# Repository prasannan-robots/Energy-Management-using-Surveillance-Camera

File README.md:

# Energy-Management-using-Surveillance-Camera
This is a project which uses camera to detect the humans and control indoor appliances

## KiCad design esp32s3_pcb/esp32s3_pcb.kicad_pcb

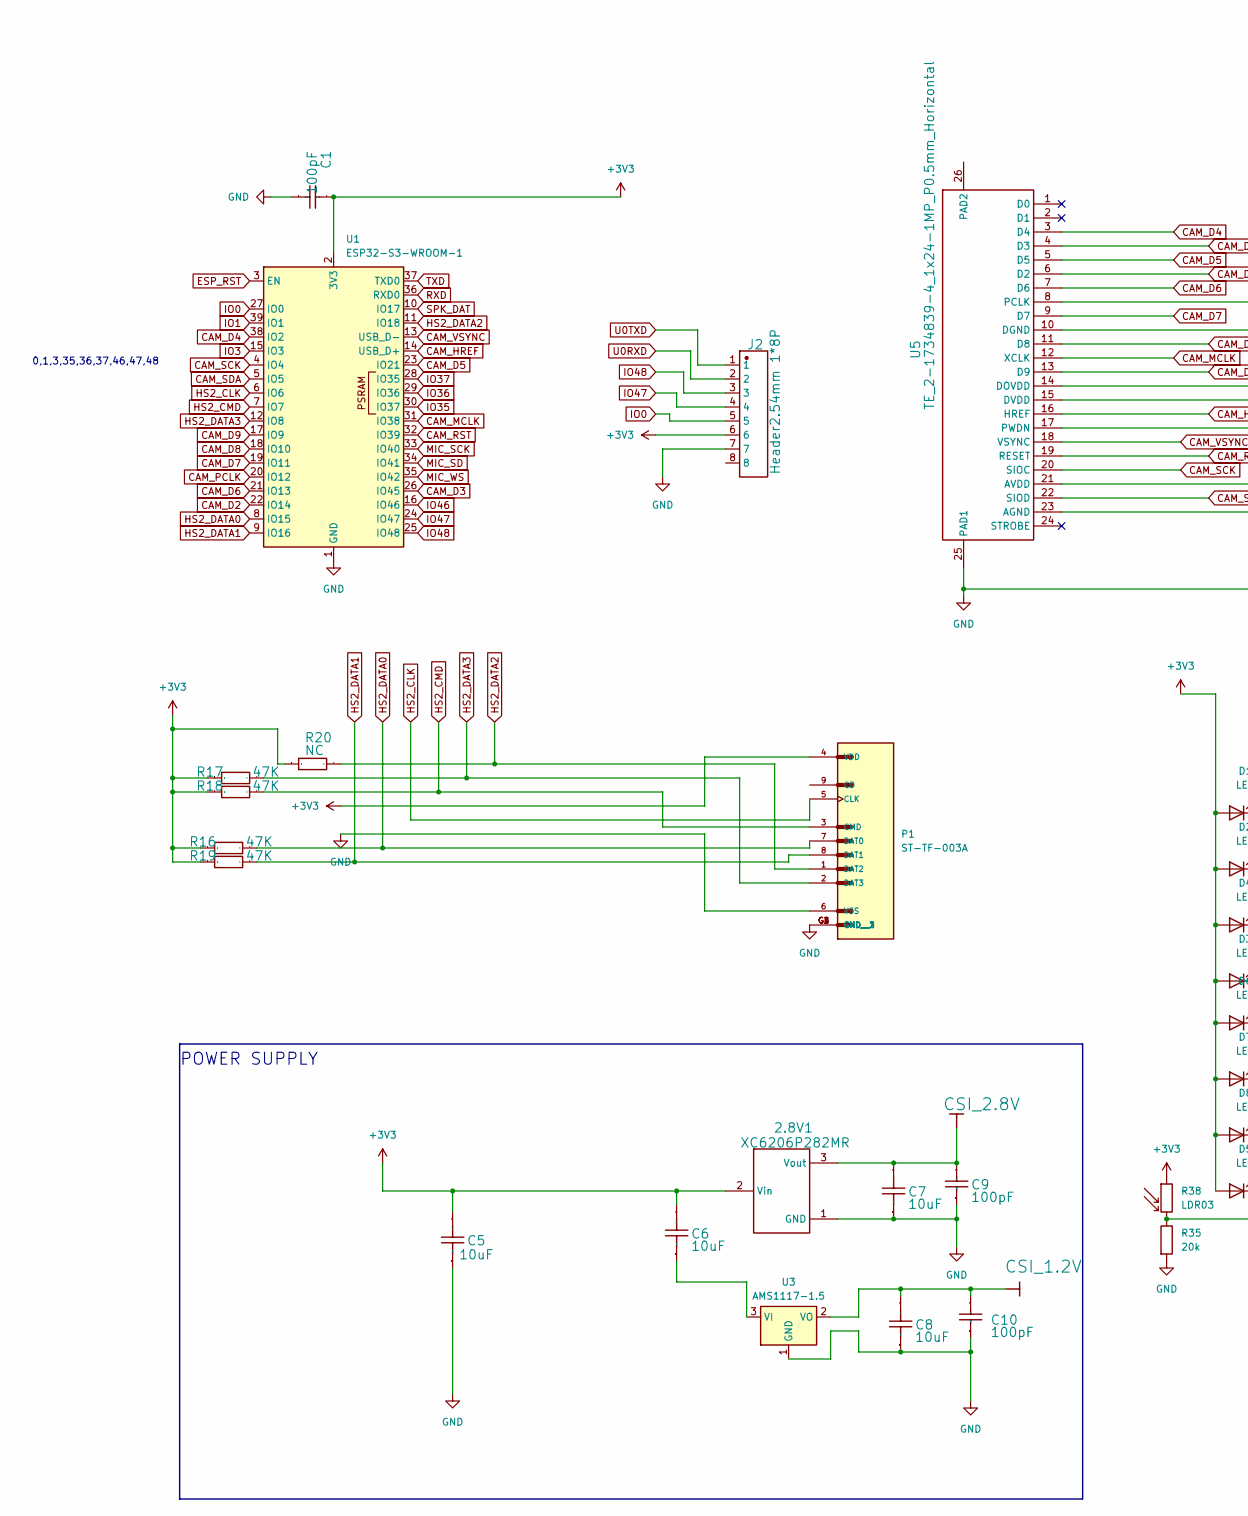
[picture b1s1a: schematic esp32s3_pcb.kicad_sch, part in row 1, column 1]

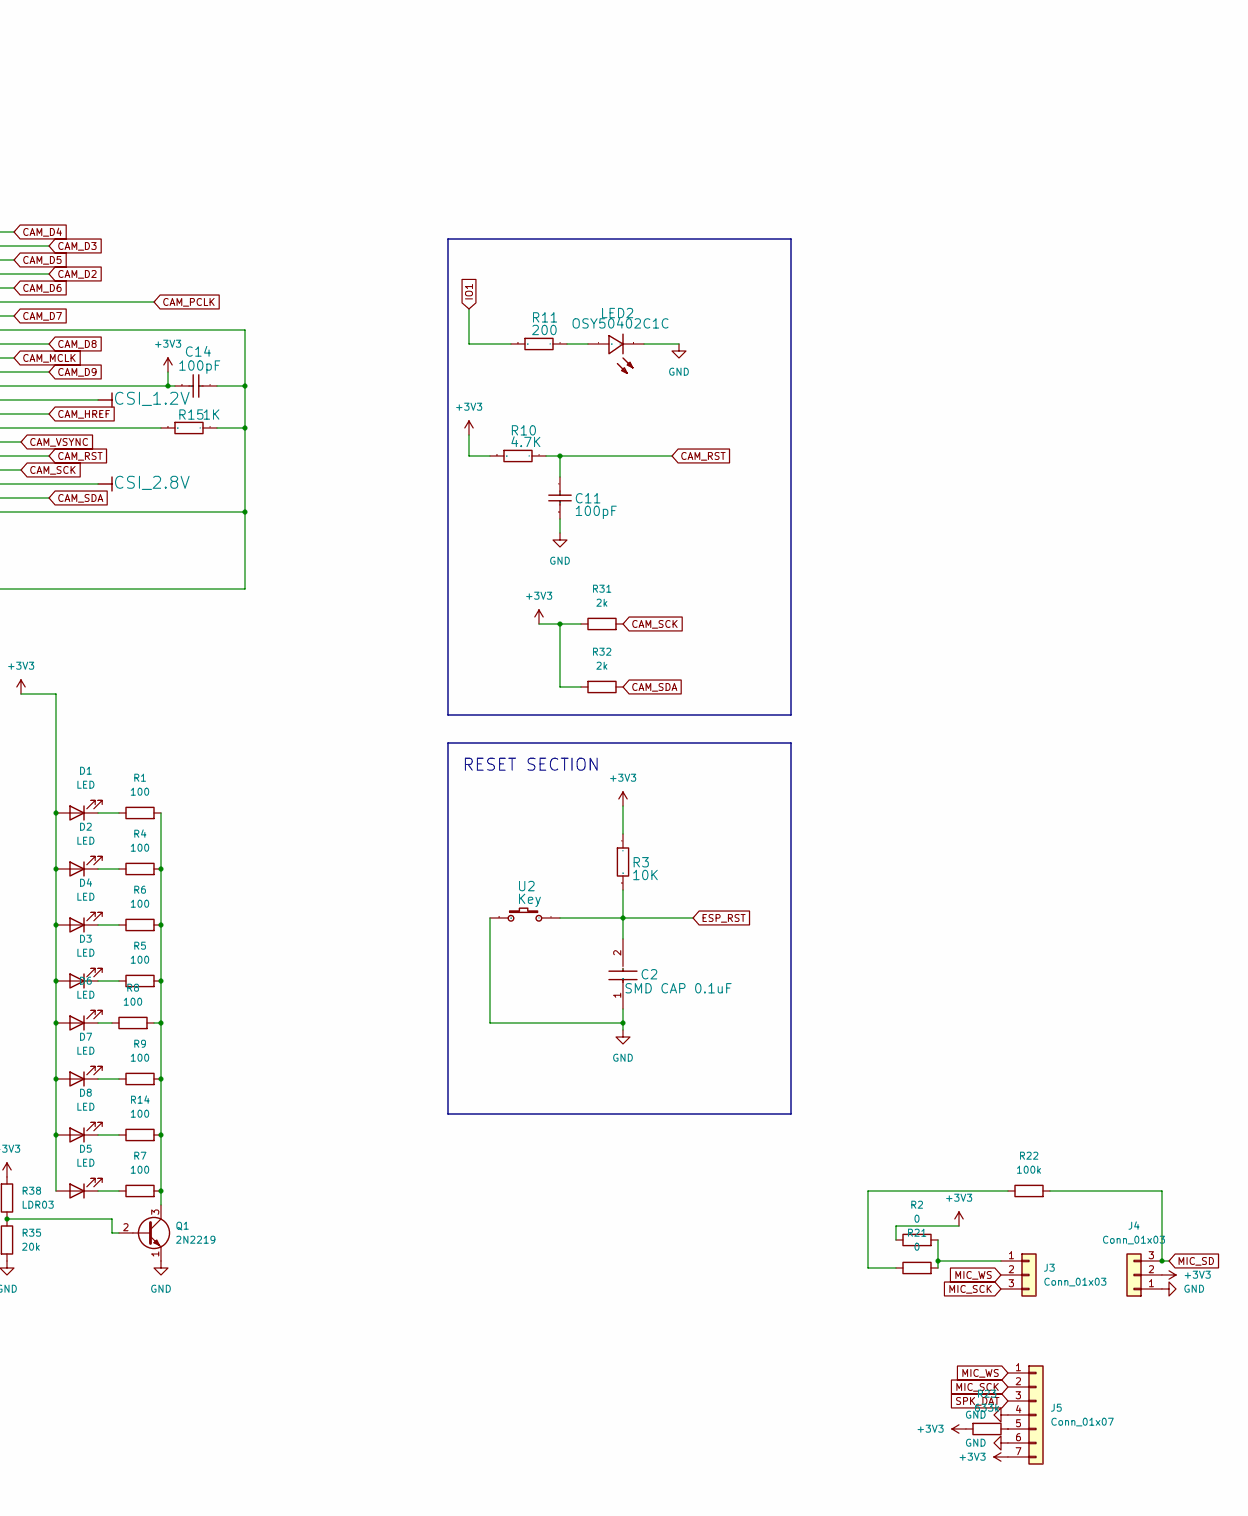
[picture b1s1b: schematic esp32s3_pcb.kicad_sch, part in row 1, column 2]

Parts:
2.8V1: XC6206P282MR; SOT-23-3; Manufacturer Part XC6206P282MR
C1, C9, C10, C11, C14: 100pF; C_0603_1608Metric; Manufacturer Part 0402CG101J500NT
C2: SMD CAP 0.1uF; C_0603_1608Metric
C5, C6, C7, C8: 10uF; C_0603_1608Metric; Manufacturer Part 0805F106M160NT
D1, D2, D3, D4, D5, D6, D7, D8: LED; LED_D5.0mm_IRGrey
J2: Header2.54mm 1*8P; PinSocket_1x08_P2.54mm_Vertical; Manufacturer Part Header2.54mm 1*8P
J3, J4: Conn_01x03; PinSocket_1x03_P2.54mm_Vertical
J5: Conn_01x07; PinSocket_1x07_P2.54mm_Vertical
LED2: OSY50402C1C; LED_D5.0mm; Manufacturer Part OSY50402C1C
P1: ST-TF-003A; SUNTECH_ST-TF-003A
Q1: 2N2219; TO-46-3_Window
R1, R4, R5, R6, R7, R8, R9, R14: 100; R_0402_1005Metric
R2, R21: 0; R_0402_1005Metric
R3: 10K; R_0805_2012Metric; Manufacturer Part RC0201JR-0710KL
R10: 4.7K; R_0402_1005Metric; Manufacturer Part 0402WGF4701TCE
R11: 200; R_0402_1005Metric; Manufacturer Part 0805W8F1001T5E
R15: 1K; R_0402_1005Metric; Manufacturer Part 0805W8F1001T5E
R16, R17, R18, R19: 47K; R_0402_1005Metric; Manufacturer Part MCR004YZPJ473
R20: NC; R_0402_1005Metric
R22: 100k; R_0402_1005Metric
R23: 633k; R_0603_1608Metric
R31, R32: 2k; R_0603_1608Metric
R35: 20k; R_0603_1608Metric
R38: LDR03; R_LDR_5.1x4.3mm_P3.4mm_Vertical
U1: ESP32-S3-WROOM-1
U2: Key; PinHeader_1x02_P2.54mm_Vertical
U3: AMS1117-1.5; SOT-89-3
U5: TE_2-1734839-4_1x24-1MP_P0.5mm_Horizontal

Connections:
+3V3: 2.8V1.2 (Vin), C1.2, C5.2, C6.2, C14.1, D1.2 (A), D2.2 (A), D3.2 (A), D4.2 (A), D5.2 (A), D6.2 (A), D7.2 (A), D8.2 (A), J2.6, J4.2, J5.7, P1.4 (VDD), R2.1, R3.2, R10.1, R16.1, R17.1, R18.1, R19.1, R20.1, R23.2, R31.1, R32.2, R38.1, U1.2 (3V3), U5.14 (DOVDD)
CAM_D2: U1.22 (IO14), U5.6 (D2)
CAM_D3: U1.26 (IO45), U5.4 (D3)
CAM_D4: U1.38 (IO2), U5.3 (D4)
CAM_D5: U1.23 (IO21), U5.5 (D5)
CAM_D6: U1.21 (IO13), U5.7 (D6)
CAM_D7: U1.19 (IO11), U5.9 (D7)
CAM_D8: U1.18 (IO10), U5.11 (D8)
CAM_D9: U1.17 (IO9), U5.13 (D9)
CAM_HREF: U1.14 (USB_D+), U5.16 (HREF)
CAM_MCLK: U1.31 (IO38), U5.12 (XCLK)
CAM_PCLK: U1.20 (IO12), U5.8 (PCLK)
CAM_RST: C11.2, R10.2, U1.32 (IO39), U5.19 (RESET)
CAM_SCK: R31.2, U1.4 (IO4), U5.20 (SIOC)
CAM_SDA: R32.1, U1.5 (IO5), U5.22 (SIOD)
CAM_VSYNC: U1.13 (USB_D-), U5.18 (VSYNC)
CSI_1.2V: C8.2, C10.2, U3.2 (VO), U5.15 (DVDD)
CSI_2.8V: 2.8V1.3 (Vout), C7.2, C9.2, U5.21 (AVDD)
ESP_RST: C2.2, R3.1, U1.3 (EN), U2.2
GND: 2.8V1.1 (GND), C1.1, C2.1, C5.1, C7.1, C8.1, C9.1, C10.1, C11.1, C14.2, J2.7, J4.1, J5.4, J5.6, LED2.1 (C), P1.6 (VSS), P1.G1 (GND), P1.G2 (GND__1), P1.G3 (GND__2), P1.G4 (GND__3), Q1.1 (E), R15.2, R35.2, U1.1 (GND), U1.40 (GND), U1.41 (GND), U2.1, U3.1 (GND), U5.10 (DGND), U5.23 (AGND), U5.25 (PAD1)
HS2_CLK: P1.5 (CLK), U1.6 (IO6)
HS2_CMD: P1.3 (CMD), R18.2, U1.7 (IO7)
HS2_DATA0: P1.7 (DAT0), R16.2, U1.8 (IO15)
HS2_DATA1: P1.8 (DAT1), R19.2, U1.9 (IO16)
HS2_DATA2: P1.1 (DAT2), R20.2, U1.11 (IO18)
HS2_DATA3: P1.2 (DAT3), R17.2, U1.12 (IO8)
IO0: J2.5, U1.27 (IO0)
IO1: R11.1, U1.39 (IO1)
IO3: U1.15 (IO3)
IO35: U1.30 (IO37)
IO36: U1.29 (IO36)
IO37: U1.28 (IO35)
IO46: U1.16 (IO46)
IO47: J2.4, U1.24 (IO47)
IO48: J2.3, U1.25 (IO48)
MIC_SCK: J3.3, J5.2, U1.33 (IO40)
MIC_SD: J4.3, R22.2, U1.34 (IO41)
MIC_WS: J3.2, J5.1, U1.35 (IO42)
unnamed: D1.1 (K), R1.1
unnamed: D2.1 (K), R4.1
unnamed: D3.1 (K), R5.1
unnamed: D4.1 (K), R6.1
unnamed: D5.1 (K), R7.1
unnamed: D6.1 (K), R8.1
unnamed: D7.1 (K), R9.1
unnamed: D8.1 (K), R14.1
unnamed: J3.1, R2.2, R21.2
unnamed: J5.5, R23.1
unnamed: LED2.2 (A), R11.2
unnamed: Q1.2 (B), R35.1, R38.2
unnamed: Q1.3 (C), R1.2, R4.2, R5.2, R6.2, R7.2, R8.2, R9.2, R14.2
unnamed: R21.1, R22.1
unnamed: C6.1, U3.3 (VI)
unnamed: R15.1, U5.17 (PWDN)
RXD: U1.36 (RXD0)
SPK_DAT: J5.3, U1.10 (IO17)
TXD: U1.37 (TXD0)
U0RXD: J2.2
U0TXD: J2.1

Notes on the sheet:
RESET SECTION
0,1,3,35,36,37,46,47,48
POWER SUPPLY

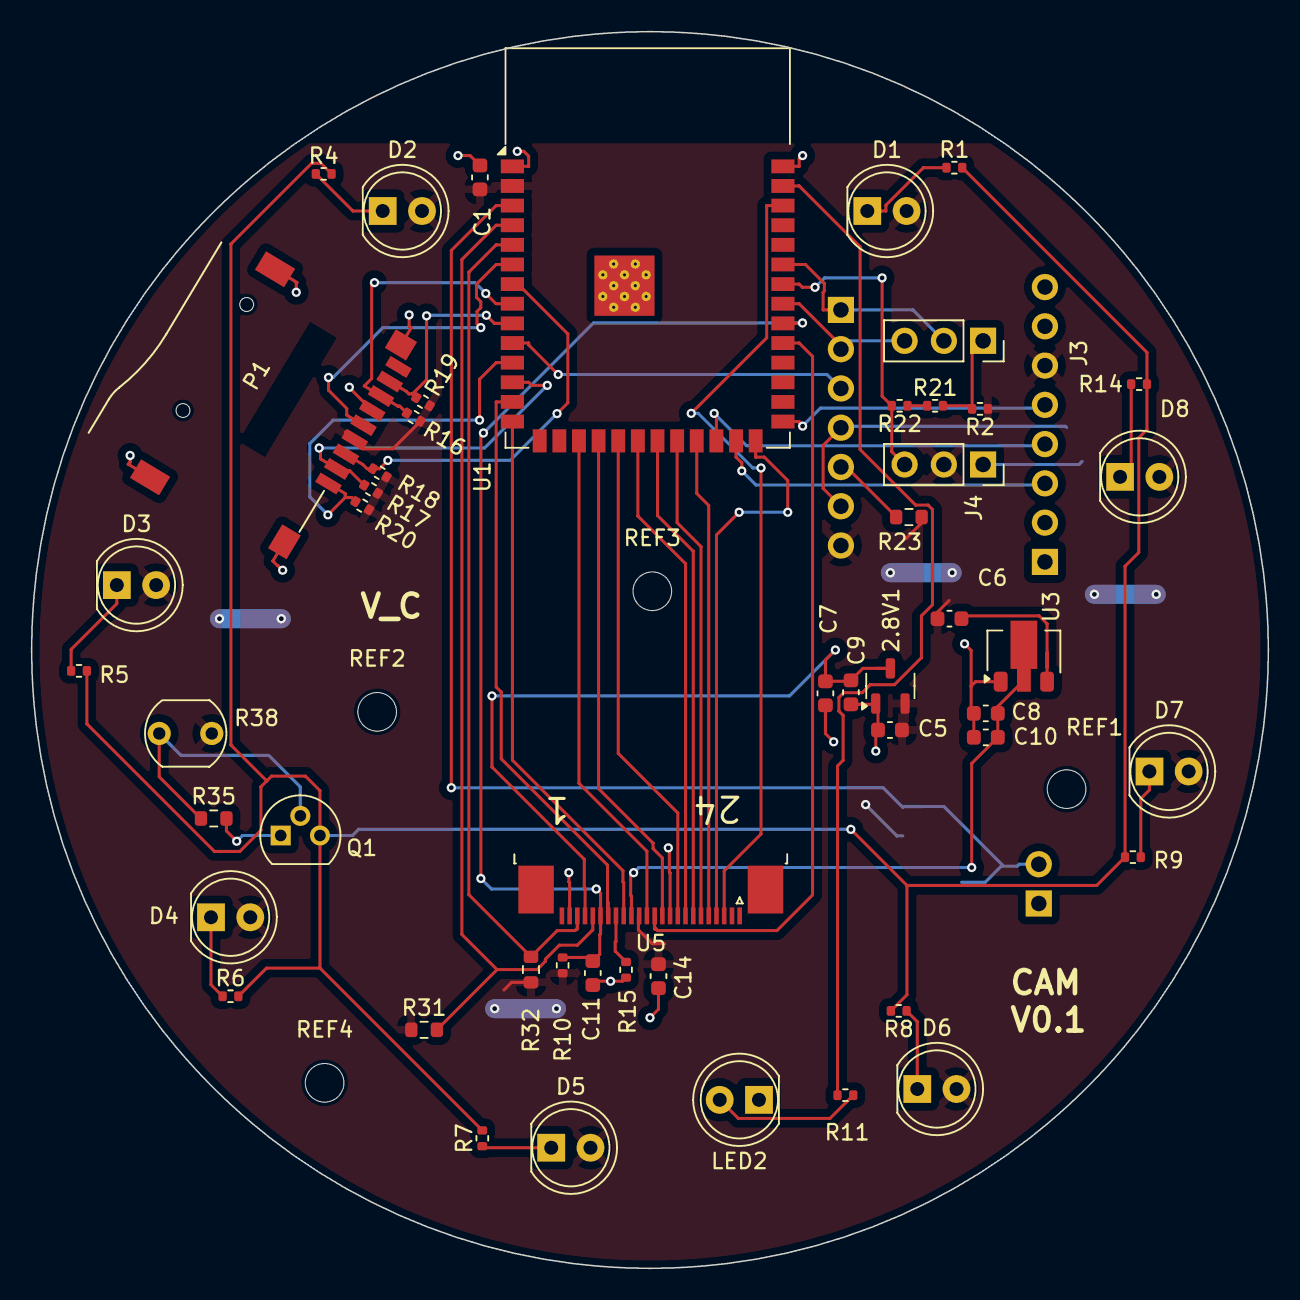
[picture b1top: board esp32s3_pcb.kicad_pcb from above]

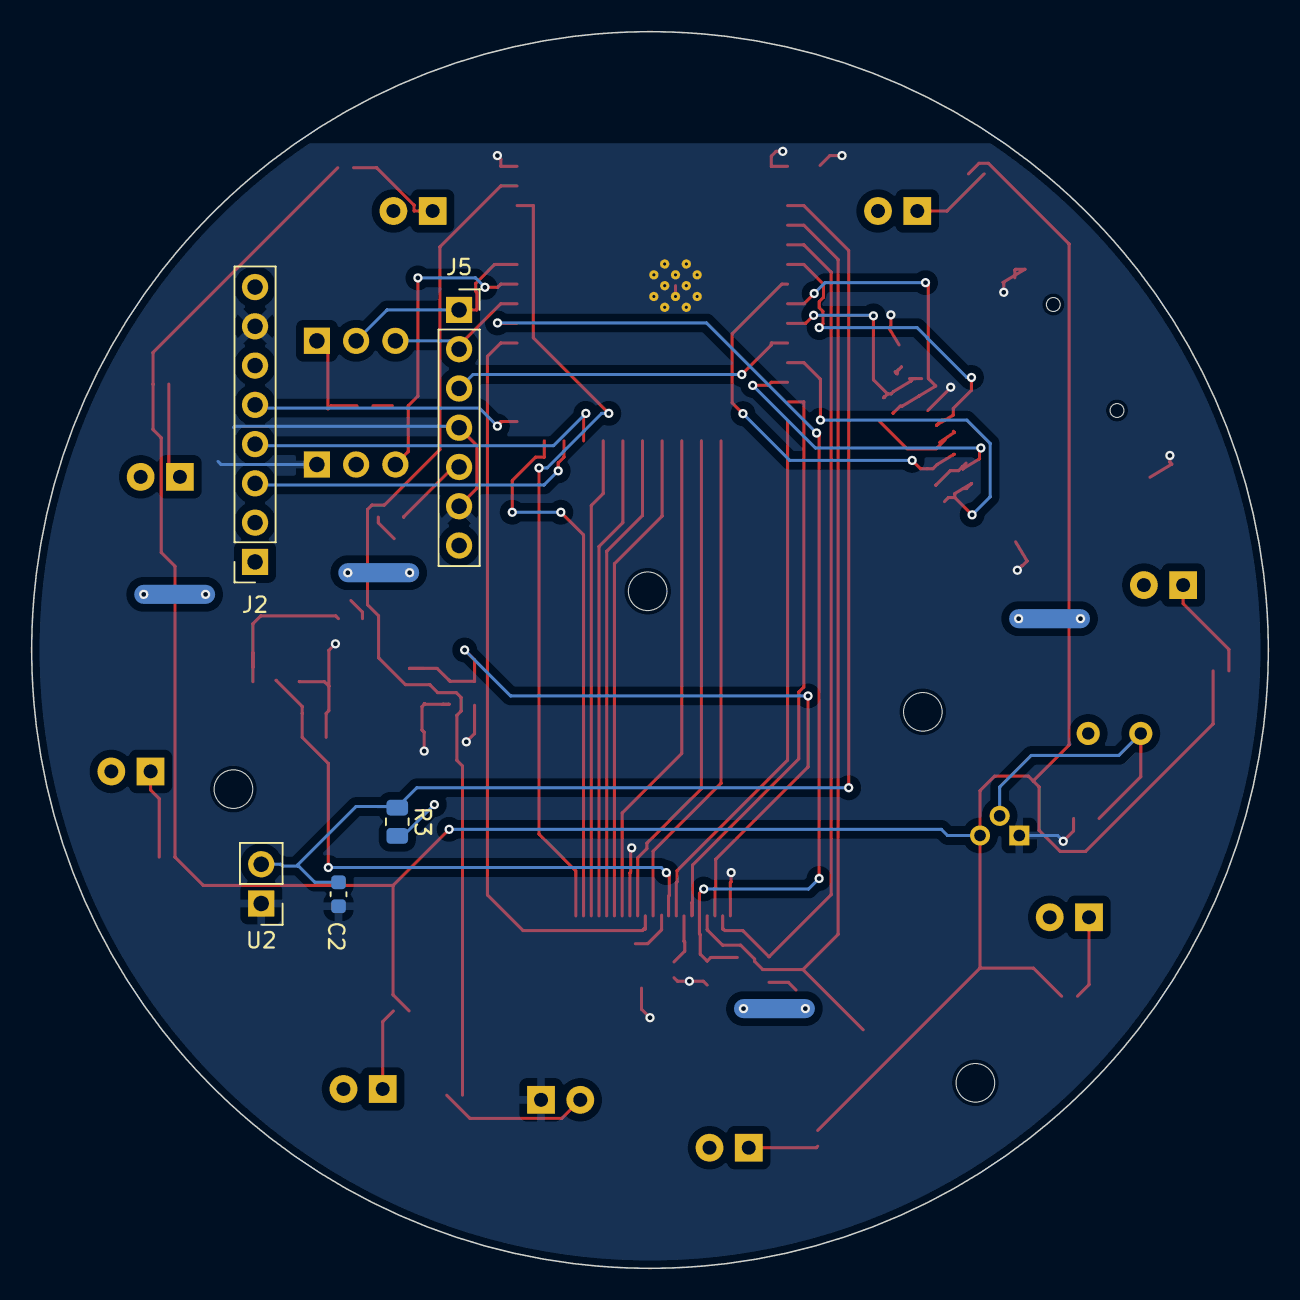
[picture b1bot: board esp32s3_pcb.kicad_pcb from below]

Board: 2 copper layers, 80.0 x 80.0 mm, 59 parts (5 on the bottom side), 50 nets.

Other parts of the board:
REF1, REF2, REF3, REF4: MountingHole_2.5mm

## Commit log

2025-08-18 First
2025-11-28 streamer
2025-11-28 added one slide
2025-11-28 check this
